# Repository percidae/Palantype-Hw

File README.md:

# Palantype-HW
Affordable Palantype Hardware

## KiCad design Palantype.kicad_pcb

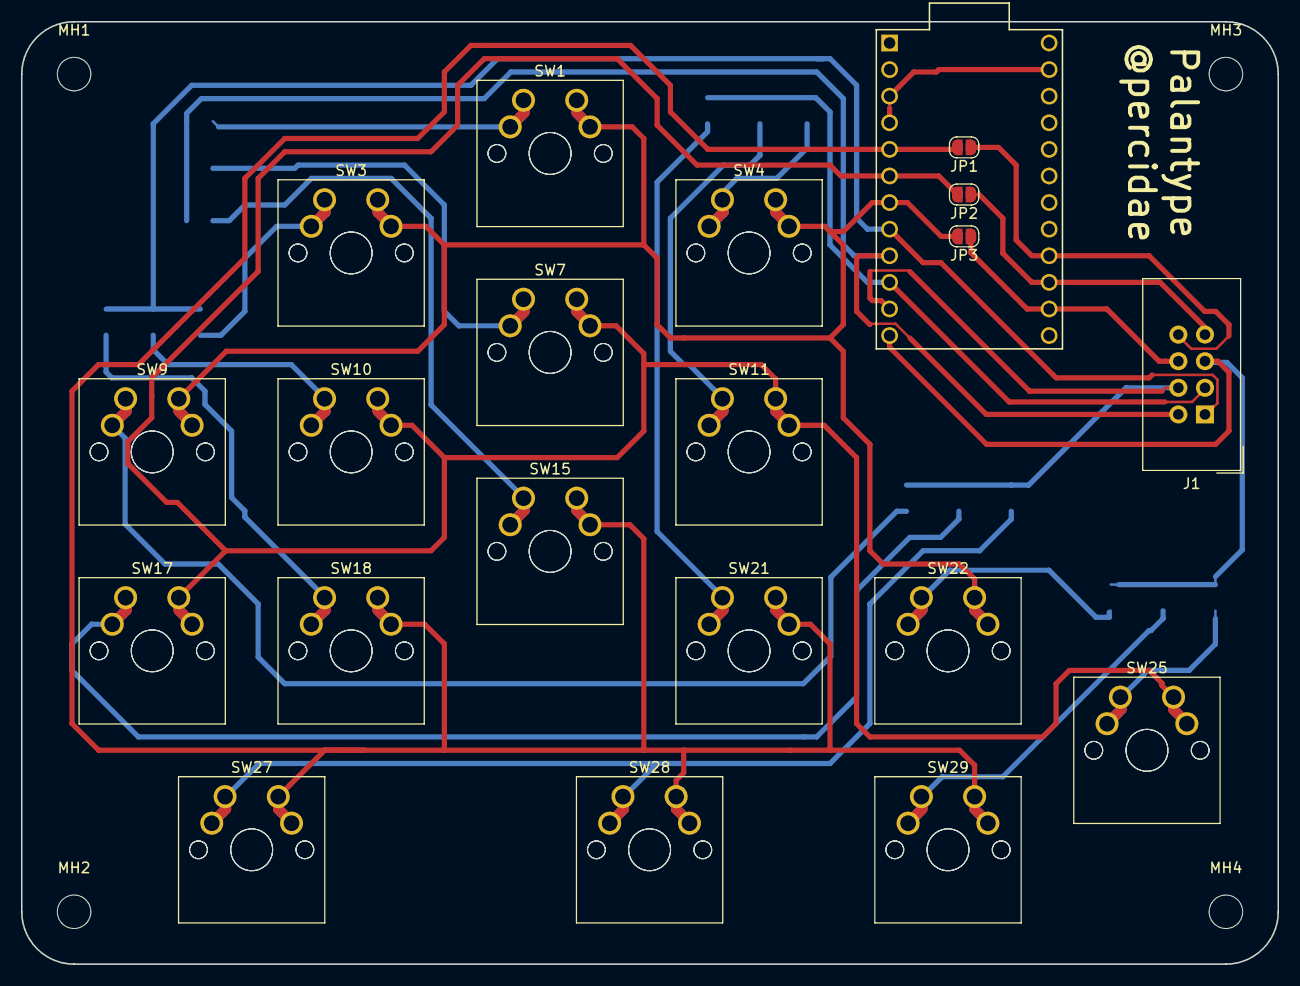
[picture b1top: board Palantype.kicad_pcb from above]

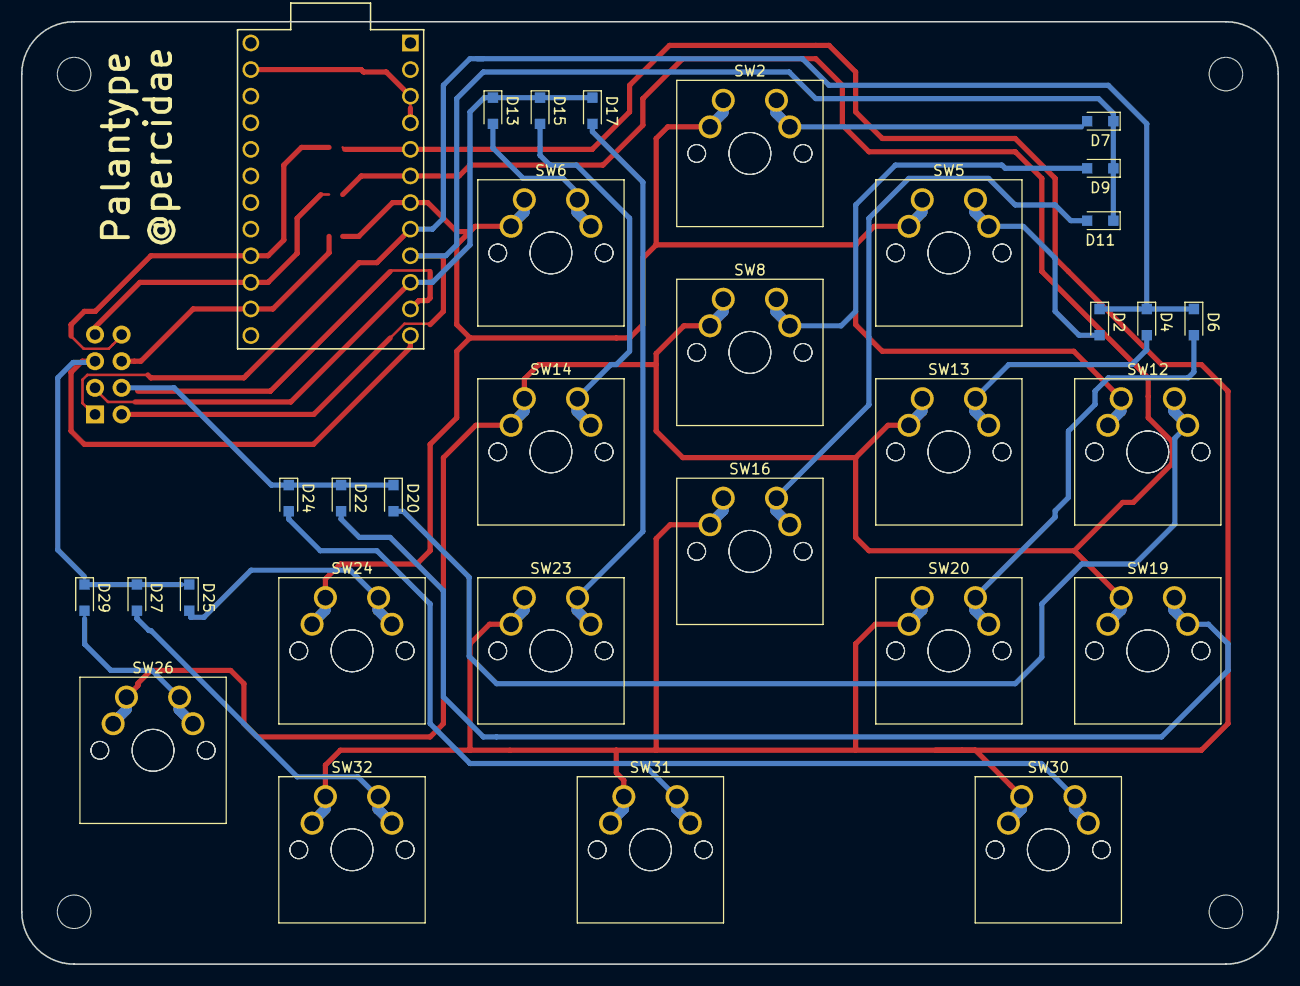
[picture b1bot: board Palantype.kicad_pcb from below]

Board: 2 copper layers, 120.0 x 90.0 mm, 56 parts (31 on the bottom side), 27 nets.

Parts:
D2, D4, D6, D7, D9, D11, D13, D15, D17, D20, D22, D24, D25, D27, D29: 1N4148; D_SOD-323_HandSoldering
J1: Conn_02x04_Odd_Even; IDC-Header_2x04_P2.54mm_Vertical
JP1, JP2, JP3: SolderJumper_2_Open; SolderJumper-2_P1.3mm_Open_RoundedPad1.0x1.5mm
MH1, MH2, MH3, MH4: MountingHole; MountingHole_3.2mm_M3
SW1, SW2, SW3, SW4, SW5, SW6, SW7, SW8, SW9, SW10, SW11, SW12, SW13, SW14, SW15, SW16, SW17, SW18, SW19, SW20, SW21, SW22, SW23, SW24, SW25, SW26, SW27, SW28, SW29, SW30, SW31, SW32: SW_Push; SW_Cherry_MX1A_1.00u_PCB
U1: ProMicro

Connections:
/Column_1: D20.1, D22.1, D24.1, J1.4, U1.11
/Column_2: D2.1, D4.1, D6.1, J1.1, U1.8
/Column_3: D7.1, D9.1, D11.1, J1.2, U1.9
/Column_4: D13.1, D15.1, D17.1, J1.3, U1.10
/Column_5: D25.1, D27.1, D29.1, J1.5, U1.12
/Row_1: JP1.2, SW15.1, SW16.2, SW18.1, SW20.2, SW21.1, SW23.2, SW27.1, SW28.1, SW29.1, SW30.2, SW31.2, SW32.2, U1.5
/Row_2: JP2.2, SW7.1, SW8.2, SW10.1, SW11.1, SW13.2, SW14.2, SW17.1, SW19.2, SW25.1, SW26.2, U1.6
/Row_3: JP3.2, SW1.1, SW2.2, SW3.1, SW4.1, SW5.2, SW6.2, SW9.1, SW12.2, SW22.1, SW24.2, U1.7
/Row_4: J1.8, JP1.1, U1.16
/Row_5: J1.7, JP2.1, U1.15
/Row_6: J1.6, JP3.1, U1.14
GND: U1.3, U1.4, U1.23
unnamed: D2.2, SW3.2, SW5.1
unnamed: D4.2, SW10.2, SW13.1
unnamed: D6.2, SW18.2, SW20.1
unnamed: D7.2, SW1.2, SW2.1
unnamed: D9.2, SW7.2, SW8.1
unnamed: D11.2, SW15.2, SW16.1
unnamed: D13.2, SW4.2, SW6.1
unnamed: D15.2, SW11.2, SW14.1
unnamed: D17.2, SW21.2, SW23.1
unnamed: D20.2, SW9.2, SW12.1
unnamed: D22.2, SW17.2, SW19.1
unnamed: D24.2, SW27.2, SW28.2, SW30.1, SW31.1
unnamed: D25.2, SW22.2, SW24.1
unnamed: D27.2, SW29.2, SW32.1
unnamed: D29.2, SW25.2, SW26.1

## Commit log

2018-08-10 v0.1
